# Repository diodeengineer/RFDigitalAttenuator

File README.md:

## RF Digital Attenuator (ESP32)
A custom-designed digital RF attenuator controlled by a bare ESP32 microcontroller. This project integrates wireless control with precision RF signal conditioning on a single PCB.

## Features
Microcontroller: Bare ESP32 for compact integration.

RF Control: Digital step attenuation for signal power management.

Connectivity: Wi-Fi/Bluetooth enabled for remote signal adjustment.

Design Tool: Created using KiCad 8.0 (or current version).

## Project Structure
/esp-c3-RF.kicad_pcb: PCB layout files with RF considerations (impedance matching).

/esp-c3-RF.kicad_sch: Schematic design including the ESP32-C3 peripheral circuitry.

/Schema.pdf: High-level view of the circuit design.

/LIB_STF202-22T1G: Footprints/Symbols for specific components.

## 🛠 Hardware Details
The design focuses on maintaining signal integrity for RF paths. Key design choices include:

Impedance Matching: 50 ohm traces for RF input/output.

Power Supply: Integrated LDO to provide clean power to the C3 chip and attenuator IC.

Antenna: On-board PCB antenna.

## 📝 To-Do / Roadmap
[ ] Finalize PCB routing and ground plane stitching.

[ ] Order prototype via Lion Circuits.

[ ] Develop firmware for Web-based attenuation control.

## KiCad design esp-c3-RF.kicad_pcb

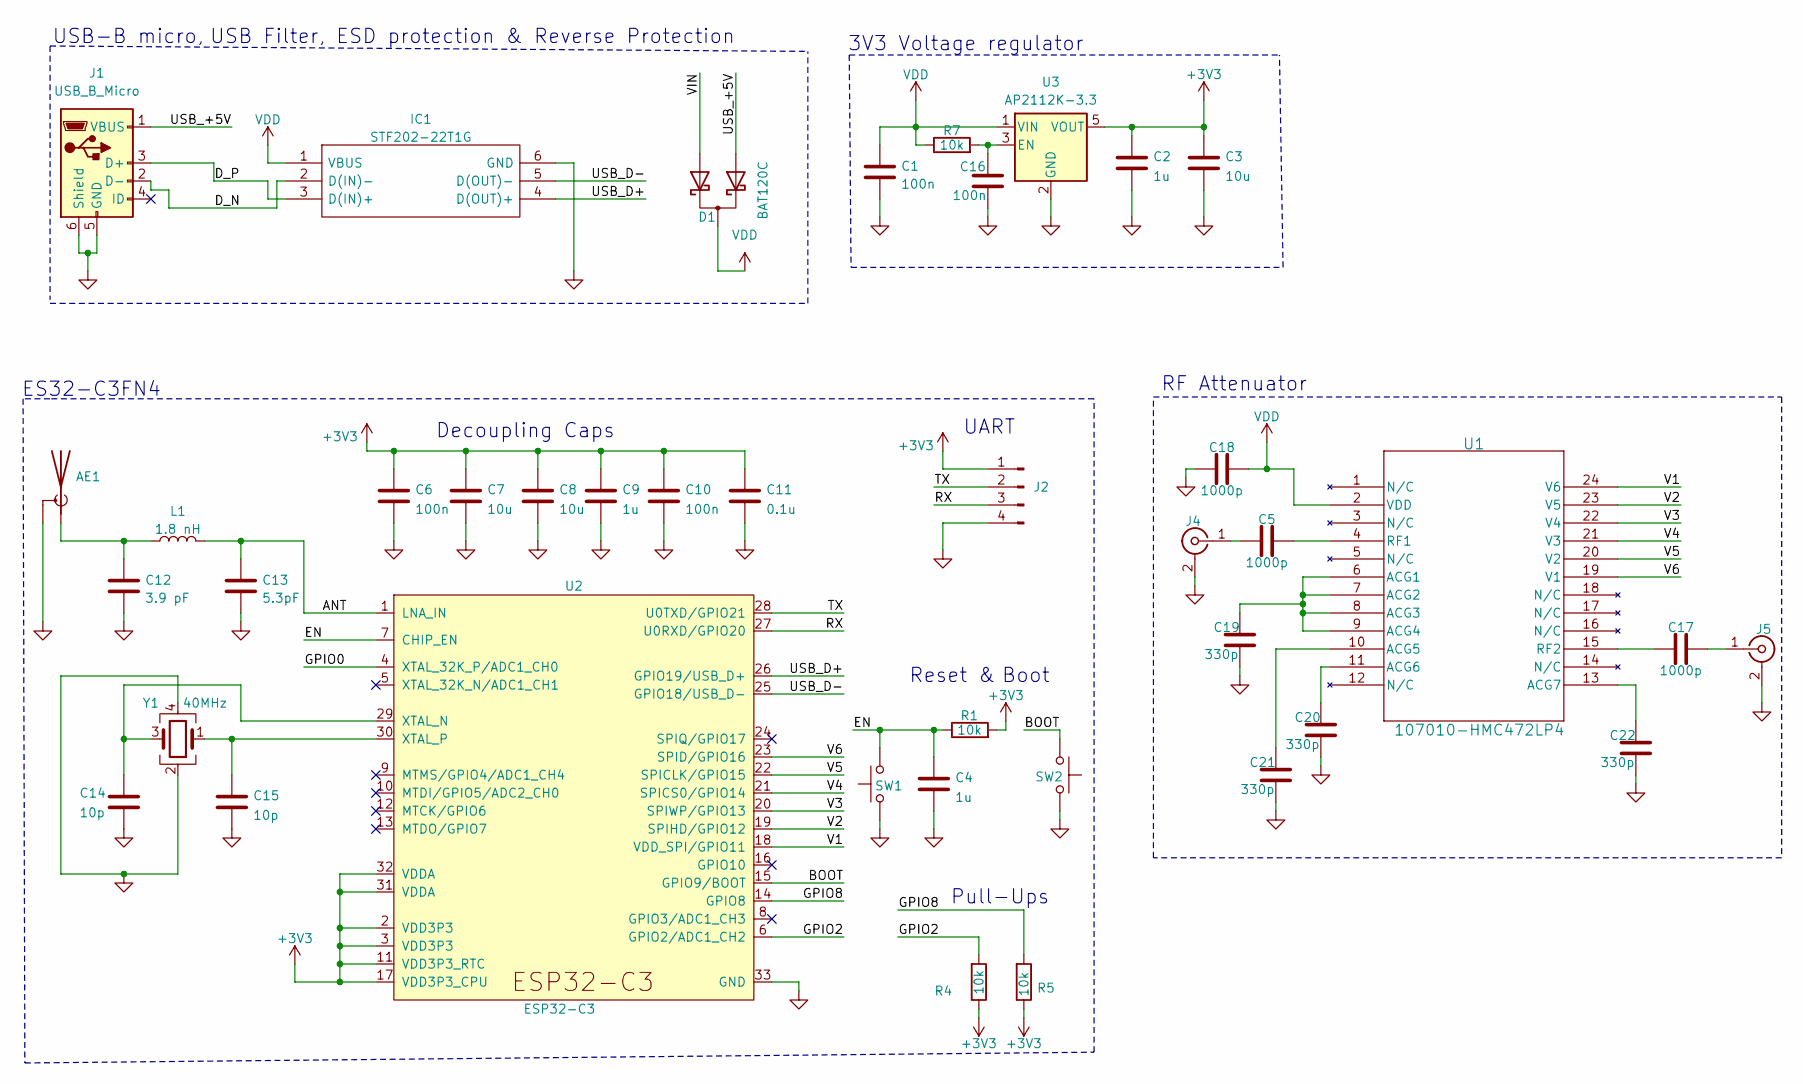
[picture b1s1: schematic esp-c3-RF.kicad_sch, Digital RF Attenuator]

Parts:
AE1: Antenna_Shield; ESPRESSIF_ESP32_MIFA_2.4GHz_Right
C1, C6, C10, C16: 100n; C_0603_1608Metric
C2, C4, C9: 1u; C_0603_1608Metric
C3, C7, C8: 10u; C_0603_1608Metric
C5, C17, C18: 1000p; C_0603_1608Metric
C11: 0.1u; C_0603_1608Metric
C12: 3.9 pF; C_0603_1608Metric
C13: 5.3pF; C_0603_1608Metric
C14, C15: 10p; C_0603_1608Metric
C19, C20, C21, C22: 330p; C_0603_1608Metric
D1: BAT120C; SOT-223
IC1: STF202-22T1G; SOT95P275X110-6N; Manufacturer_Part_Number STF202-22T1G; Mouser Part Number 863-STF202-22T1G
J1: USB_B_Micro; USB_Micro-B_GCT_USB3076-30-A
J2: Conn_01x04_Pin; PinHeader_1x04_P2.54mm_Vertical
J4, J5: Conn_Coaxial; SMA_Samtec_SMA-J-P-H-ST-EM1_EdgeMount
L1: 1.8 nH; L_0603_1608Metric
R1, R4, R5, R7: 10k; R_0603_1608Metric
SW1, SW2: SW_Push; SW_SPST_PTS810
U1: 107010-HMC472LP4; SMT_24_ADI
U2: ESP32-C3; QFN-32-1EP_5x5mm_P0.5mm_EP3.45x3.45mm
U3: AP2112K-3.3; SOT-23-5
Y1: 40MHz; Crystal_SMD_2016-4Pin_2.0x1.6mm

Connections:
+3V3: C2.1, C3.1, C6.1, C7.1, C8.1, C9.1, C10.1, C11.1, J2.1, R1.2, R4.1, R5.1, U2.2 (VDD3P3), U2.3 (VDD3P3), U2.11 (VDD3P3_RTC), U2.17 (VDD3P3_CPU), U2.31 (VDDA), U2.32 (VDDA), U3.5 (VOUT)
/ANT: C13.1, L1.1, U2.1 (LNA_IN)
/BOOT: SW2.1, U2.15 (GPIO9/BOOT)
/D_N: IC1.2 (D(IN)-), J1.2 (D-)
/D_P: IC1.3 (D(IN)+), J1.3 (D+)
/EN: C4.1, R1.1, SW1.2, U2.7 (CHIP_EN)
/GPIO0: U2.4 (XTAL_32K_P/ADC1_CH0)
/GPIO2: R4.2, U2.6 (GPIO2/ADC1_CH2)
/GPIO8: R5.2, U2.14 (GPIO8)
/RX: J2.3, U2.27 (U0RXD/GPIO20)
/TX: J2.2, U2.28 (U0TXD/GPIO21)
/USB_+5V: D1.1 (A1), J1.1 (VBUS); also elsewhere on the board
/USB_D+: IC1.4 (D(OUT)+), U2.26 (GPIO19/USB_D+)
/USB_D-: IC1.5 (D(OUT)-), U2.25 (GPIO18/USB_D-)
/V1: U1.24 (V6), U2.18 (VDD_SPI/GPIO11)
/V2: U1.23 (V5), U2.19 (SPIHD/GPIO12)
/V3: U1.22 (V4), U2.20 (SPIWP/GPIO13)
/V4: U1.21 (V3), U2.21 (SPICS0/GPIO14)
/V5: U1.20 (V2), U2.22 (SPICLK/GPIO15)
/V6: U1.19 (V1), U2.23 (SPID/GPIO16)
/VIN: D1.3 (A2)
GND: AE1.2 (Shield), C1.2, C2.2, C3.2, C4.2, C6.2, C7.2, C8.2, C9.2, C10.2, C11.2, C12.2, C13.2, C14.2, C15.2, C16.2, C18.1, C19.2, C20.2, C21.2, C22.2, IC1.6 (GND), J1.5 (GND), J1.6 (Shield), J2.4, J4.2 (Ext), J5.2 (Ext), SW1.1, SW2.2, U2.33 (GND), U3.2 (GND), Y1.2, Y1.4; also elsewhere on the board
unnamed: AE1.1 (A), C12.1, L1.2
unnamed: C5.1, J4.1 (In)
unnamed: C17.2, J5.1 (In)
unnamed: C19.1, U1.6 (ACG1), U1.7 (ACG2), U1.8 (ACG3), U1.9 (ACG4)
unnamed: C21.1, U1.10 (ACG5)
unnamed: C20.1, U1.11 (ACG6)
unnamed: C22.1, U1.13 (ACG7)
unnamed: C5.2, U1.4 (RF1)
unnamed: C17.1, U1.15 (RF2)
unnamed: C14.1, U2.29 (XTAL_N), Y1.3
unnamed: C15.1, U2.30 (XTAL_P), Y1.1
unnamed: C16.1, R7.2, U3.3 (EN)
VDD: C1.1, C18.2, D1.4 (K), IC1.1 (VBUS), R7.1, U1.2 (VDD), U3.1 (VIN)

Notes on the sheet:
3V3 Voltage regulator
Reset & Boot
Decoupling Caps
UART
ES32-C3FN4
USB-B micro, USB Filter, ESD protection & Reverse Protection
RF Attenuator
Pull-Ups

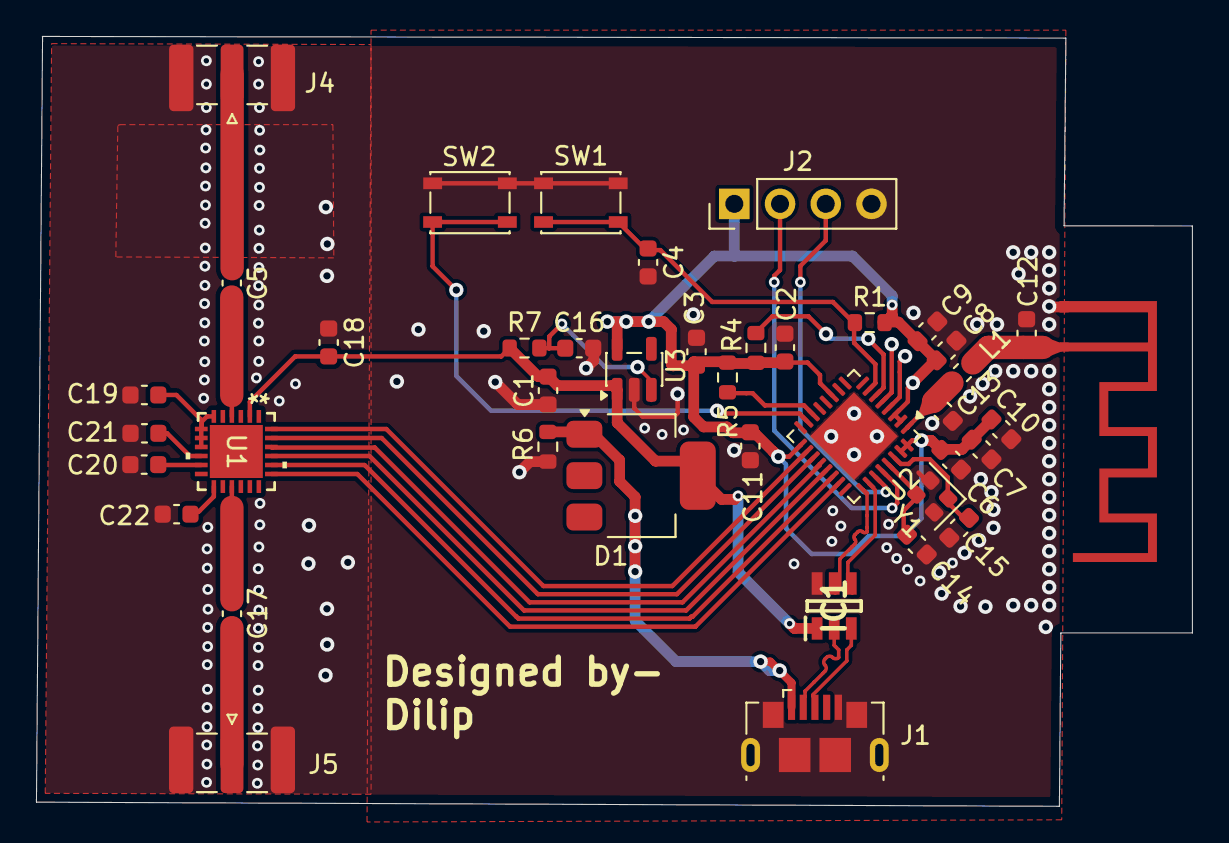
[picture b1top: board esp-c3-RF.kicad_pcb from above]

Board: 2 copper layers, 64.2 x 42.8 mm, 41 parts (0 on the bottom side), 33 nets.

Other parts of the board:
R6: 10k; R_0603_1608Metric

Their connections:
/USB_+5V: R6.1; also elsewhere on the board
GND: R6.2; also elsewhere on the board
